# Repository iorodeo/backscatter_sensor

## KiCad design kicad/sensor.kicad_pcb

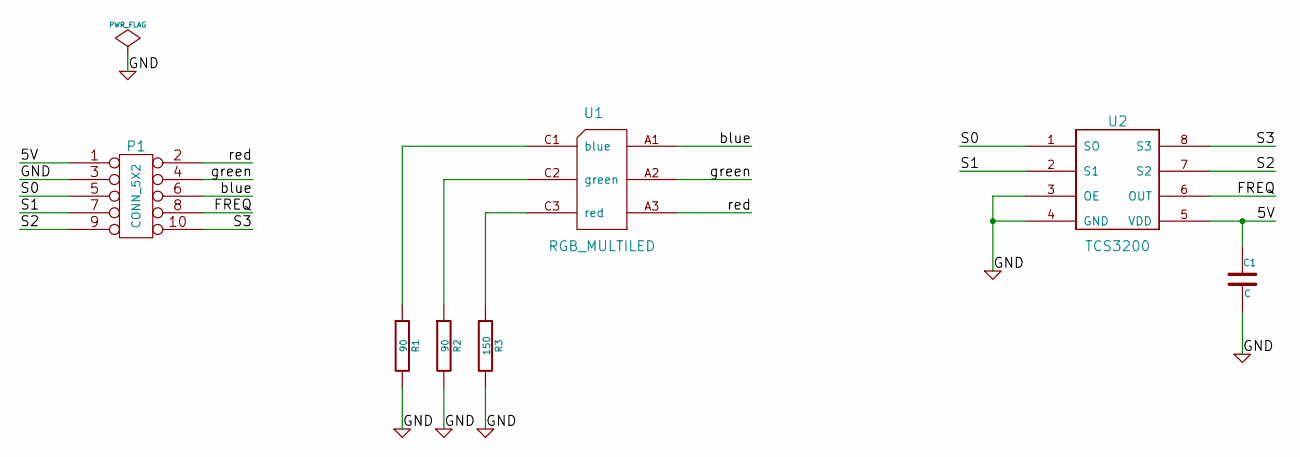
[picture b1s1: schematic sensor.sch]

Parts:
C1: C
P1: CONN_5X2
R1, R2: 90
R3: 150
U1: RGB_MULTILED
U2: TCS3200

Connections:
/5V: C1.1, P1.1, U2.5 (VDD)
/FREQ: P1.8, U2.6 (OUT)
/S0: P1.5, U2.1 (SO)
/S1: P1.7, U2.2 (S1)
/S2: P1.9, U2.7 (S2)
/S3: P1.10, U2.8 (S3)
/blue: P1.6, U1.A1
/green: P1.4, U1.A2
/red: P1.2, U1.A3
GND: C1.2, P1.3, R1.2, R2.2, R3.2, U2.3 (OE), U2.4 (GND)
unnamed: R2.1, U1.C2 (green)
unnamed: R3.1, U1.C3 (red)
unnamed: R1.1, U1.C1 (blue)

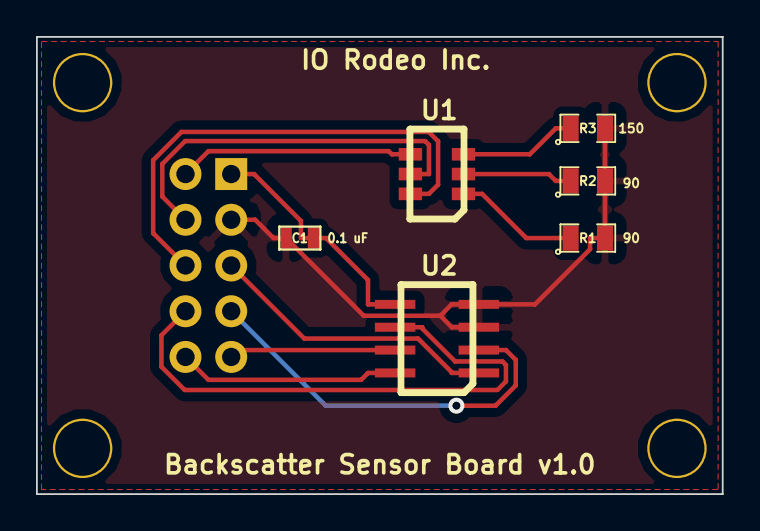
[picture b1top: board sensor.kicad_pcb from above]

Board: 2 copper layers, 38.1 x 25.4 mm, 11 parts (1 on the bottom side), 13 nets.

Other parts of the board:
MOUNT_HOLE_1, MOUNT_HOLE_2, MOUNT_HOLE_3, MOUNT_HOLE_4: VAL**; MOUNT_HOLE_4_40

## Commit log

2013-08-29 Project creation.
2013-09-09 Modified enclosure design for backscatter sensor. Included jig to make machining operations easier.
2013-09-25 Added preliminary version of mask and top plate for backscatter sensor.
2014-03-21 Added the SVG file for colorimeter mount.
